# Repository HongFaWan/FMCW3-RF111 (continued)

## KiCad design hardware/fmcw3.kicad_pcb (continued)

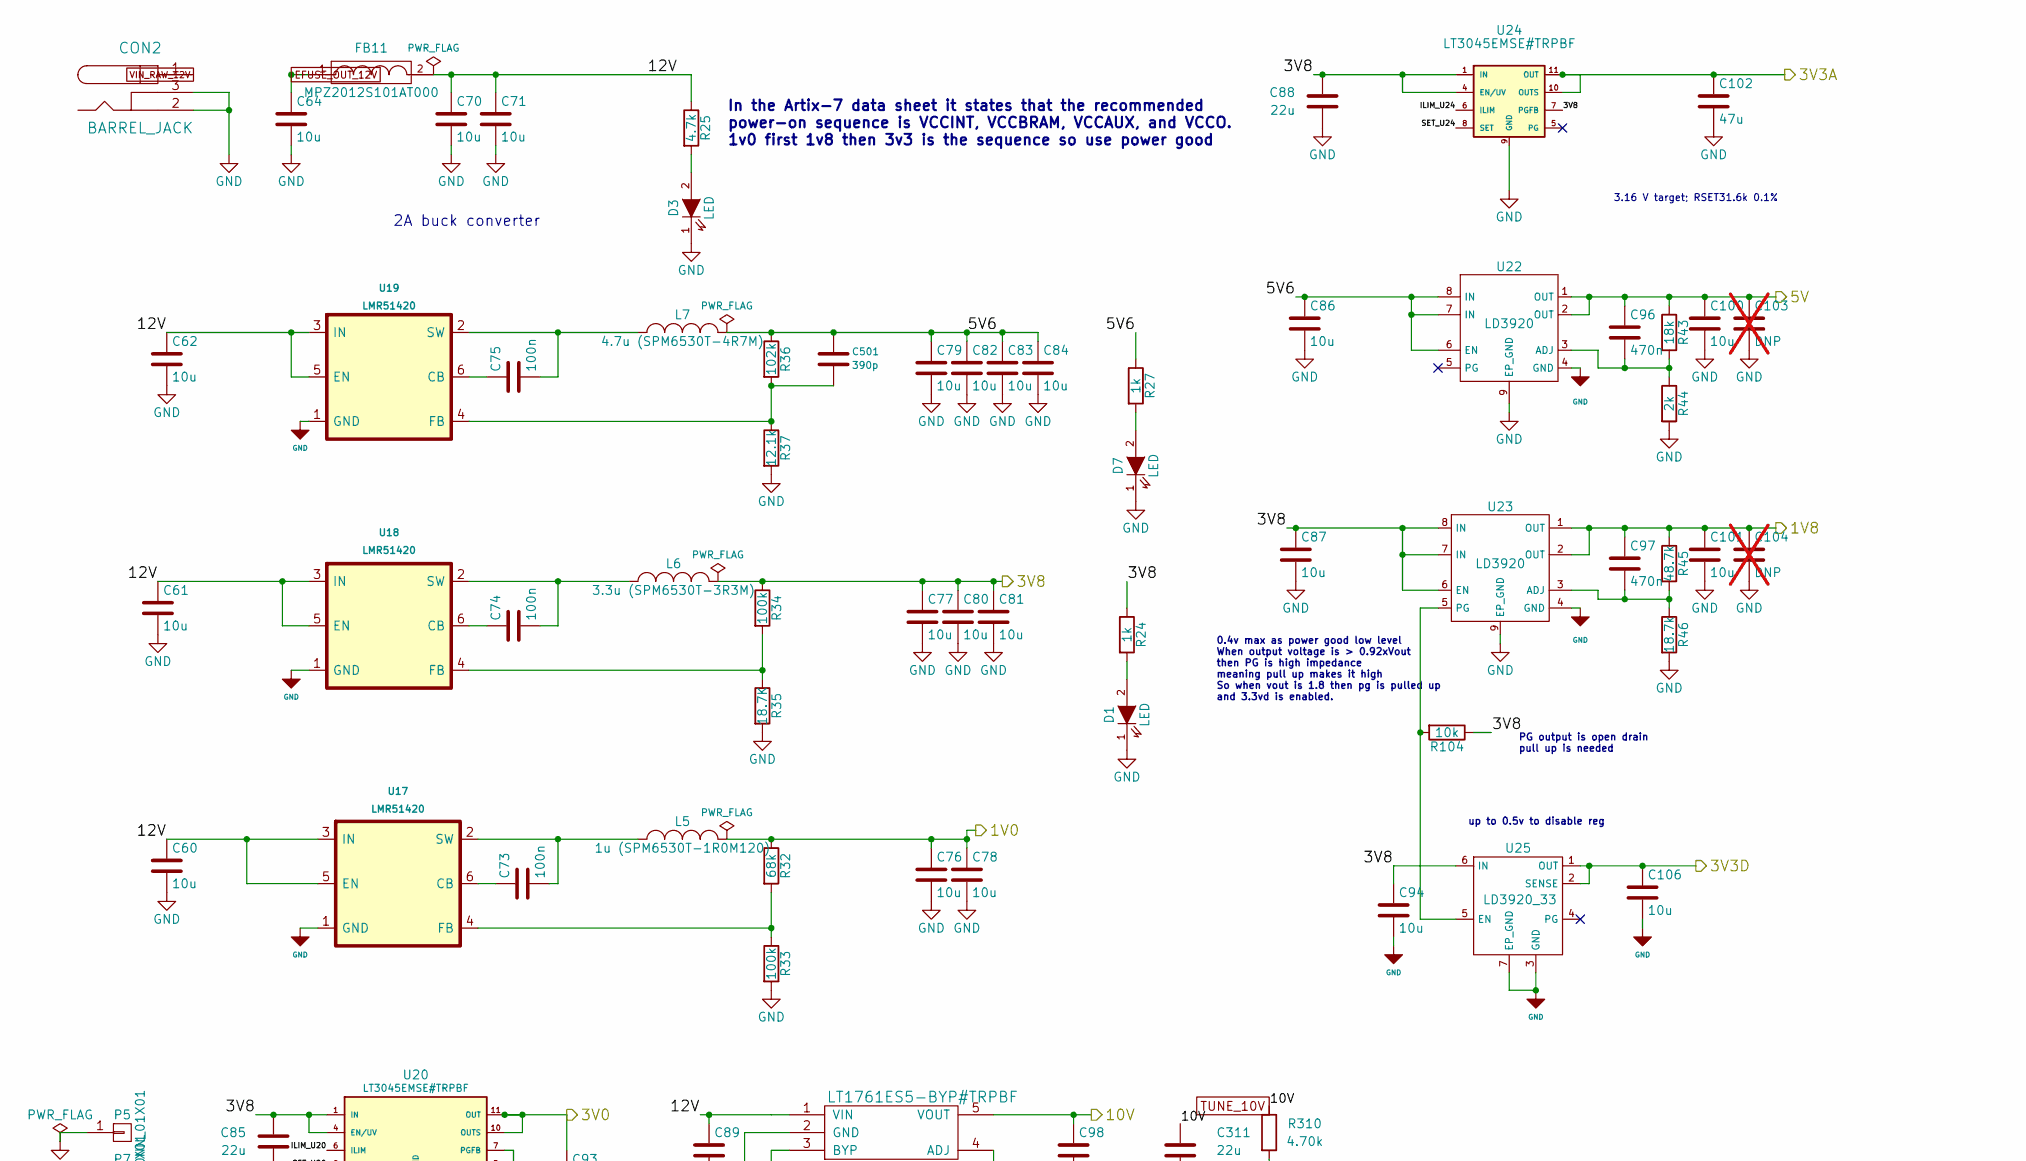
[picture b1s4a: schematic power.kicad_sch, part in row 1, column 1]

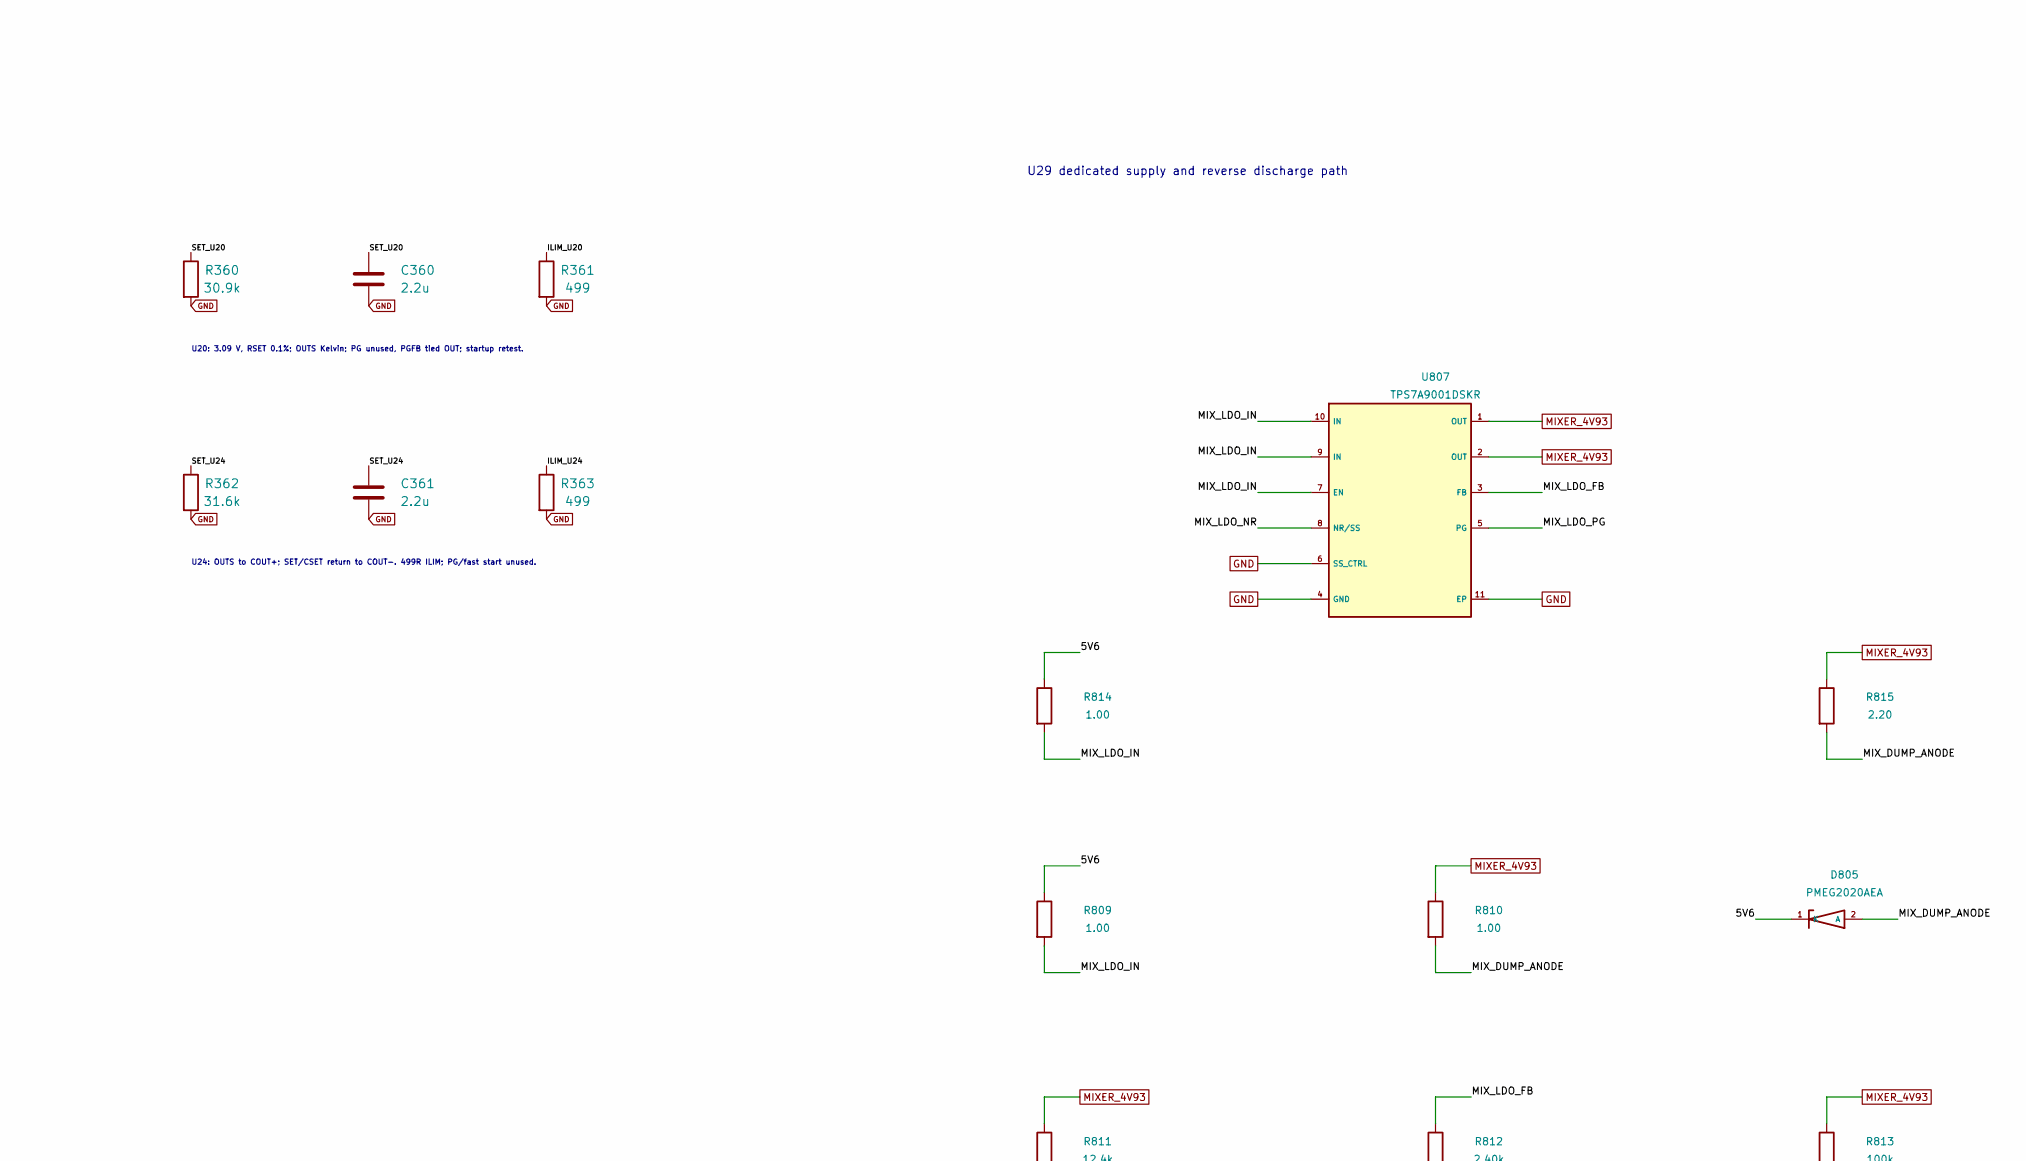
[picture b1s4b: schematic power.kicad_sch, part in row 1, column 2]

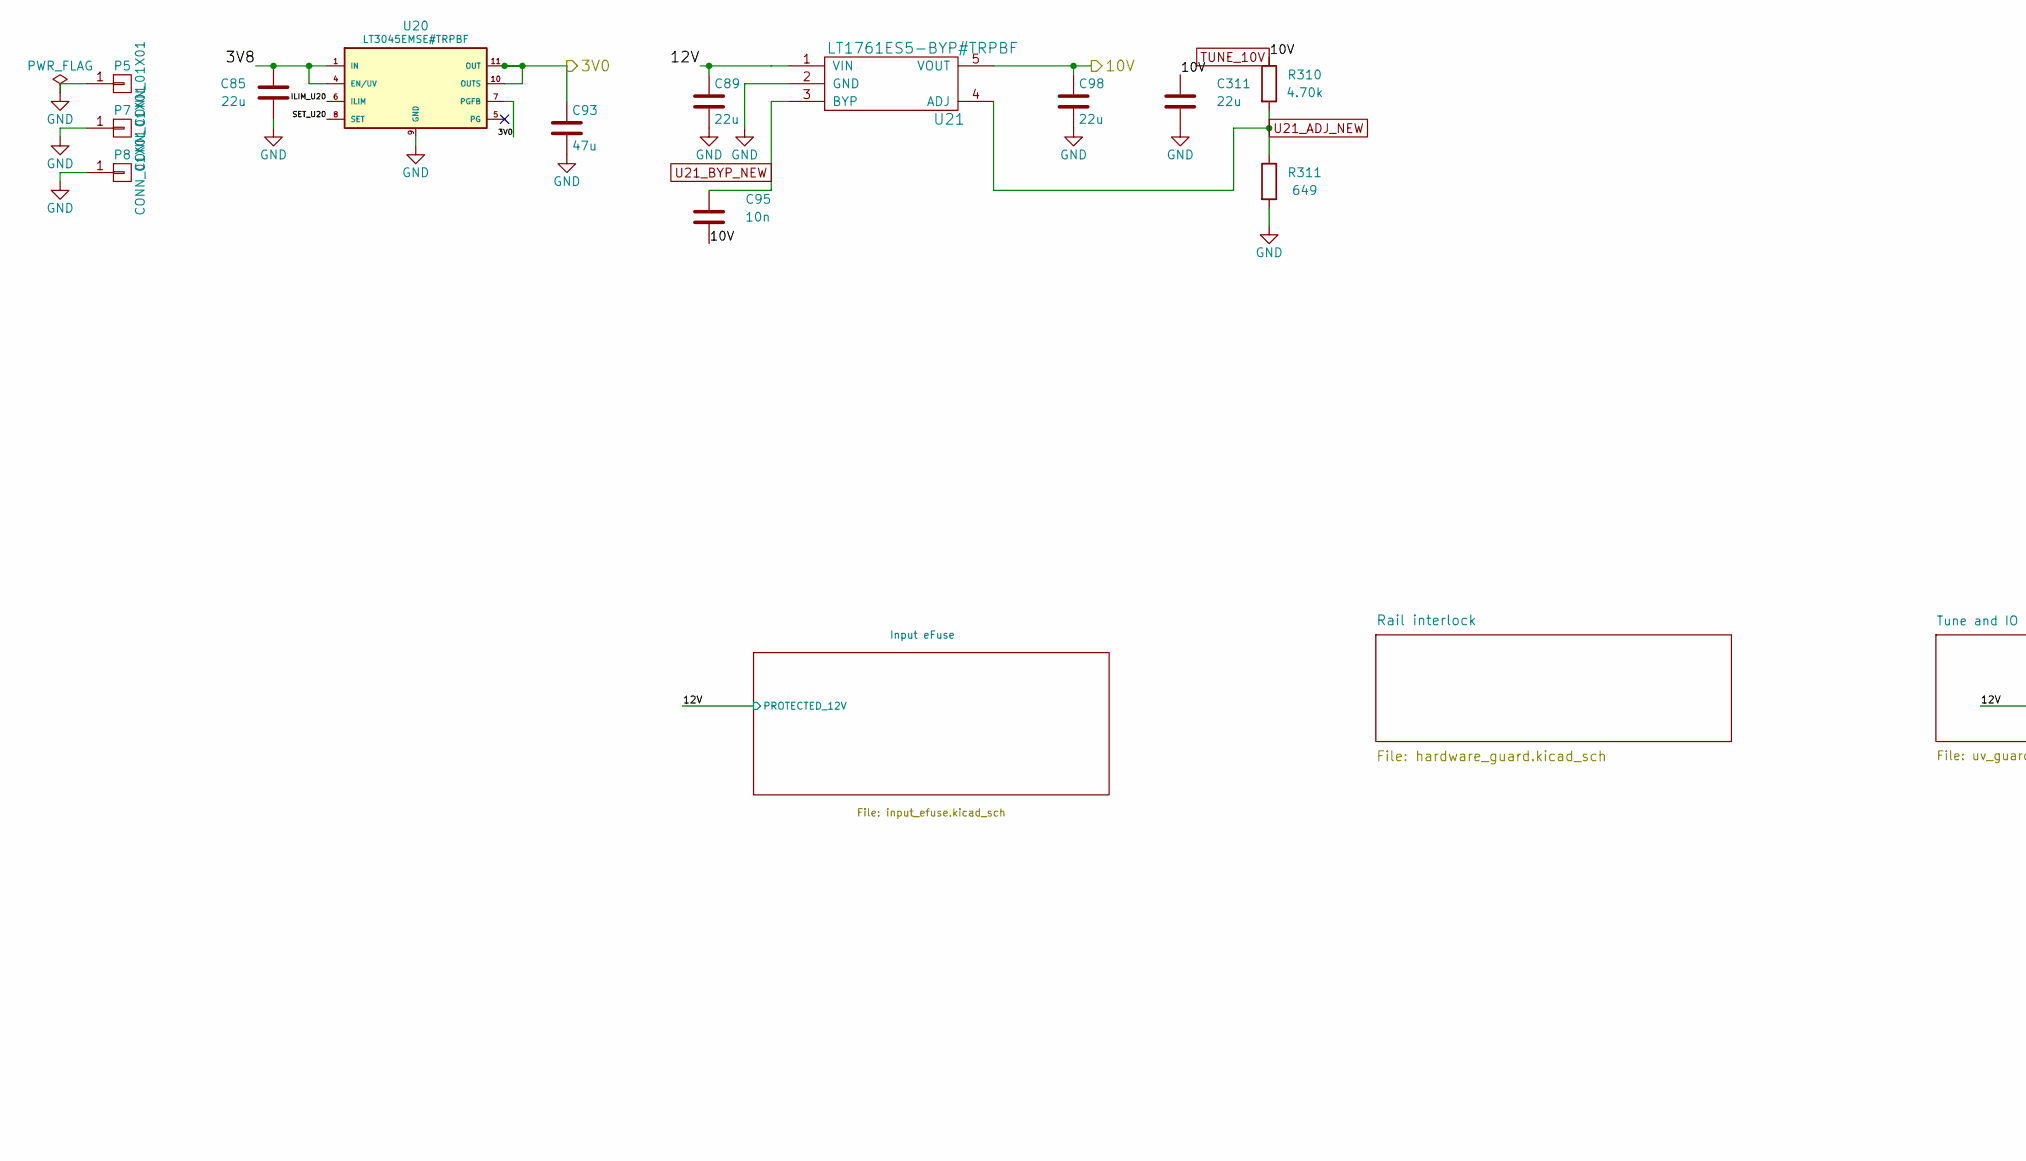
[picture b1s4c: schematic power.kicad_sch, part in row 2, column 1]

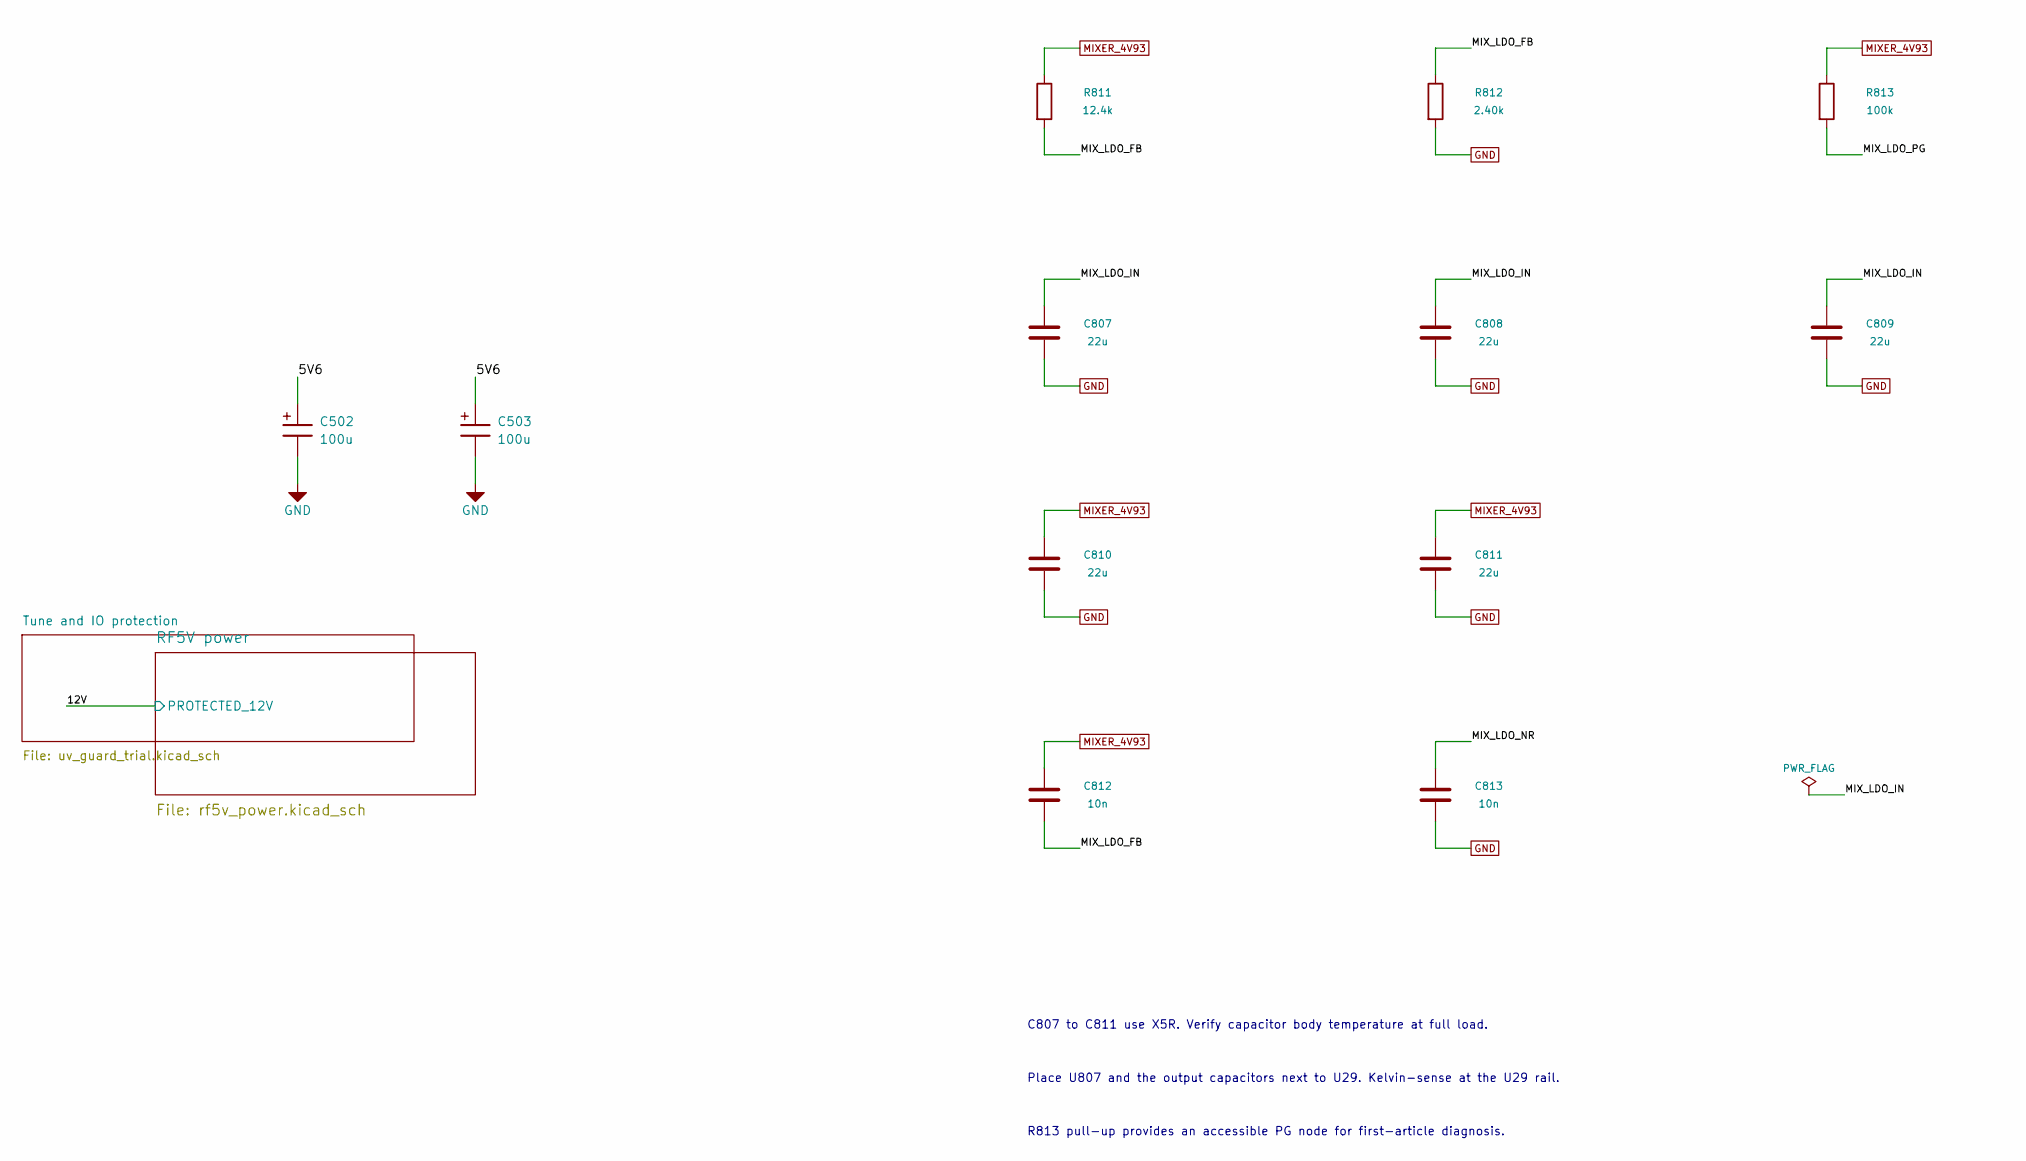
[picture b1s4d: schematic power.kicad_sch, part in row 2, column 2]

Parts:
C60, C61, C62, C64, C70, C71, C76, C77, C78, C79, C80, C81, C82, C83, C84, C86, C87, C94, C100, C101, C106: 10u; SMD_0805
C73, C74, C75: 100n; SMD_0402
C85, C88: 22u; C0805_Murata_GRM21
C89, C311: 22u; C0805_ECO
C93, C102: 47u; C1206_Murata_GRM31
C95: 10n; SMD_0402
C96, C97: 470n; SMD_0402
C98: 22u; SMD_0805
C103, C104: DNP; SMD_0805; not fitted
C360, C361: 2.2u; C0603_Assembly_Courtyard_ECO
C501: 390p; SMD_0402; MPN GRM1555C1H391JA01D
C502, C503: 100u; CP_Panasonic_POSCAP_TQC_D2; MPN 16TQC100MD2
C807, C808, C809, C810, C811: 22u; C_0805_2012Metric; MPN C2012X5R1E226M125AC
C812, C813: 10n; C_0402_1005Metric; MPN GRM1555C1E103GE01D
CON2: BARREL_JACK; PJ002AH_SLOT35
D1, D3, D7: LED; Diode_0603
D805: PMEG2020AEA; D_SOD-323; MPN PMEG2020AEA
FB11: MPZ2012S101AT000; SMD_0805
L5: 1u (SPM6530T-1R0M120); L_TDK_SPM6530T_RF111_PROPOSAL_ONLY; MPN SPM6530T-1R0M120; LCSC C87572
L6: 3.3u (SPM6530T-3R3M); L_TDK_SPM6530T_RF111_PROPOSAL_ONLY; MPN SPM6530T-3R3M; LCSC C76856
L7: 4.7u (SPM6530T-4R7M); L_TDK_SPM6530T_RF111_PROPOSAL_ONLY; MPN SPM6530T-4R7M; LCSC C76857
P5, P7, P8: CONN_01X01; MountingHole_3.2mm_M3_Pad_Via_mod
R24, R27: 1k; SMD_0402
R25: 4.7k; SMD_0402
R32: 68k; SMD_0402
R33, R34: 100k; SMD_0402
R35: 18.7K; SMD_0402
R36: 102k; SMD_0402; Manufacturer Part Number RT0402BRD07102KL
R37: 12.1k; SMD_0402; Manufacturer Part Number ERA-2ARB1212X
R43: 18k; SMD_0402
R44: 2k; SMD_0402
R45: 48.7k; SMD_0402
R46: 18.7k; SMD_0402
R104: 10k; SMD_0402
R310: 4.70k; R0603_ECO; Tolerance and TCR 0.1%, 10 ppm/K; Manufacturer Part Number ERA-3ARB472V
R311: 649; R0603_ECO; Tolerance and TCR 0.1%, 10 ppm/K; Manufacturer Part Number RG1608N-6490-B-T5
R360: 30.9k; R0402_Yageo_Mount_V10; Tolerance 0.1%; MPN RT0402BRD0730K9L; LCSC C852715
R361, R363: 499; R0402_Yageo_Mount_V10
R362: 31.6k; R0402_Panasonic_ERA2A_Mount_RF110; Tolerance 0.1%; MPN ERA-2ARB3162X; LCSC C2090771
R809, R810, R814: 1.00; R_1206_3216Metric; MPN CRCW12061R00FKEAHP
R811: 12.4k; R_0603_1608Metric; MPN ERA3ARW1242V
R812: 2.40k; R_0603_1608Metric; MPN ERA3ARW242V
R813: 100k; R_0402_1005Metric; MPN RT0402BRD07100KL
R815: 2.20; R_1206_3216Metric; MPN CRCW12062R20FKEAHP
U17, U18, U19: LMR51420; SOT23_6
U20, U24: LT3045EMSE#TRPBF; LT3045_MSE12_MFR
U21: LT1761ES5-BYP#TRPBF; LT1761_S5
U22, U23: LD3920; DFN-8-1EP_4x4mm_P0.8mm_EP2.3x3.24mm
U25: LD3920_33; DFN-6-1EP_3x3mm_P0.95mm_EP1.7x2.6mm
U807: TPS7A9001DSKR; Texas_S-PDSO-N10_EP1.2x2mm; MPN TPS7A9001DSKR

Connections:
/1V0: C76.1, C78.1, L5.2, R32.1; also elsewhere on the board
/1V8: C97.1, C101.1, C104.1, R45.1, U23.1 (OUT), U23.2 (OUT); also elsewhere on the board
/3V0: C93.1, U20.7 (PGFB), U20.10 (OUTS), U20.11 (OUT), U20.12 (OUT); also elsewhere on the board
/3V3A: C102.1, U24.10 (OUTS), U24.11 (OUT), U24.12 (OUT); also elsewhere on the board
/3V8: C77.1, C80.1, C81.1, C85.1, C87.1, C88.1, C94.1, L6.2, R24.1, R34.1, R104.1, U20.1 (IN), U20.2 (IN), U20.3 (IN), U20.4 (EN/UV), U23.6 (EN), U23.7 (VIN), U23.8 (VIN), U24.1 (IN), U24.2 (IN), U24.3 (IN), U24.4 (EN/UV), U24.7 (PGFB), U25.6 (VIN); also elsewhere on the board
/5V: C96.1, C100.1, C103.1, R43.1, U22.1 (OUT), U22.2 (OUT); also elsewhere on the board
/power/5V6: C79.1, C82.1, C83.1, C84.1, C86.1, C501.1, C502.1, C503.1, D805.1 (K), L7.2, R27.1, R36.1, R809.1, R814.1, U22.6 (EN), U22.7 (VIN), U22.8 (VIN)
/power/12V: C60.1, C61.1, C62.1, C70.1, C71.1, C89.1, FB11.2, R25.1, U17.3 (IN), U17.5 (EN), U18.3 (IN), U18.5 (EN), U19.3 (IN), U19.5 (EN), U21.1 (IN); also elsewhere on the board
/power/ILIM_U20: R361.1, U20.6 (ILIM)
/power/ILIM_U24: R363.1, U24.6 (ILIM)
/power/MIX_DUMP_ANODE: D805.2 (A), R810.2, R815.2
/power/MIX_LDO_FB: C812.2, R811.2, R812.1, U807.3 (FB)
/power/MIX_LDO_IN: C807.1, C808.1, C809.1, R809.2, R814.2, U807.7 (EN), U807.9 (IN), U807.10 (IN)
/power/MIX_LDO_NR: C813.1, U807.8 (NR/SS)
/power/MIX_LDO_PG: R813.2, U807.5 (PG)
/power/SET_U20: C360.1, R360.1, U20.8 (SET)
/power/SET_U24: C361.1, R362.1, U24.8 (SET)
EFUSE_OUT_12V: C64.1, FB11.1; also elsewhere on the board
GND: C60.2, C61.2, C62.2, C64.2, C70.2, C71.2, C76.2, C77.2, C78.2, C79.2, C80.2, C81.2, C82.2, C83.2, C84.2, C85.2, C86.2, C87.2, C88.2, C89.2, C93.2, C94.2, C98.2, C100.2, C101.2, C102.2, C103.2, C104.2, C106.2, C311.2, C360.2, C361.2, C502.2, C503.2, C807.2, C808.2, C809.2, C810.2, C811.2, C813.2, CON2.2, CON2.3, D1.1 (K), D3.1 (K), D7.1 (K), P5.1, P7.1, P8.1, R33.2, R35.2, R37.2, R44.2, R46.2, R311.2, R360.2, R361.2, R362.2, R363.2, R812.2, U17.1 (GND), U18.1 (GND), U19.1 (GND), U20.9 (GND), U20.13 (GND), U21.2 (GND), U22.4 (GND), U22.9 (PAD), U23.4 (GND), U23.9 (PAD), U24.9 (GND), U24.13 (GND), U25.3 (GND), U25.7 (PAD), U807.4 (GND), U807.6 (SS_CTRL), U807.11 (EP); also elsewhere on the board
MIXER_4V93: C810.1, C811.1, C812.1, R810.1, R811.1, R813.1, R815.1, U807.1 (OUT), U807.2 (OUT); also elsewhere on the board
unnamed: D1.2 (A), R24.2
unnamed: D3.2 (A), R25.2
unnamed: D7.2 (A), R27.2
unnamed: C73.1, U17.6 (CB)
unnamed: R32.2, R33.1, U17.4 (FB)
unnamed: C73.2, L5.1, U17.2 (SW)
unnamed: C74.1, U18.6 (CB)
unnamed: R34.2, R35.1, U18.4 (FB)
unnamed: C74.2, L6.1, U18.2 (SW)
unnamed: C75.1, U19.6 (CB)
unnamed: C501.2, R36.2, R37.1, U19.4 (FB)
unnamed: C75.2, L7.1, U19.2 (SW)
unnamed: C96.2, R43.2, R44.1, U22.3 (ADJ)
unnamed: C97.2, R45.2, R46.1, U23.3 (ADJ)
unnamed: R104.2, U23.5 (PG), U25.5 (EN)
TUNE_10V: C95.2, C98.1, C311.1, R310.1, U21.5 (OUT); also elsewhere on the board
U21_ADJ_NEW: R310.2, R311.1, U21.4 (ADJ)
U21_BYP_NEW: C95.1, U21.3 (BYP)
VIN_RAW_12V: CON2.1; also elsewhere on the board

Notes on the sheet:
up to 0.5v to disable reg
0.4v max as power good low level When output voltage is > 0.92xVout then PG is high impedance meaning pull up makes it high So when vout is 1.8 then pg is pulled up and 3.3vd is enabled.
PG output is open drain pull up is needed
In the Artix-7 data sheet it states that the recommended power-on sequence is VCCINT, VCCBRAM, VCCAUX, and VCCO. 1v0 first 1v8 then 3v3 is the sequence so use power good
2A buck converter
3.16 V target; RSET31.6k 0.1%
U20: 3.09 V, RSET 0.1%; OUTS Kelvin; PG unused, PGFB tied OUT; startup retest.
U24: OUTS to COUT+; SET/CSET return to COUT-. 499R ILIM; PG/fast start unused.
U29 dedicated supply and reverse discharge path
C807 to C811 use X5R. Verify capacitor body temperature at full load.
Place U807 and the output capacitors next to U29. Kelvin-sense at the U29 rail.
R813 pull-up provides an accessible PG node for first-article diagnosis.

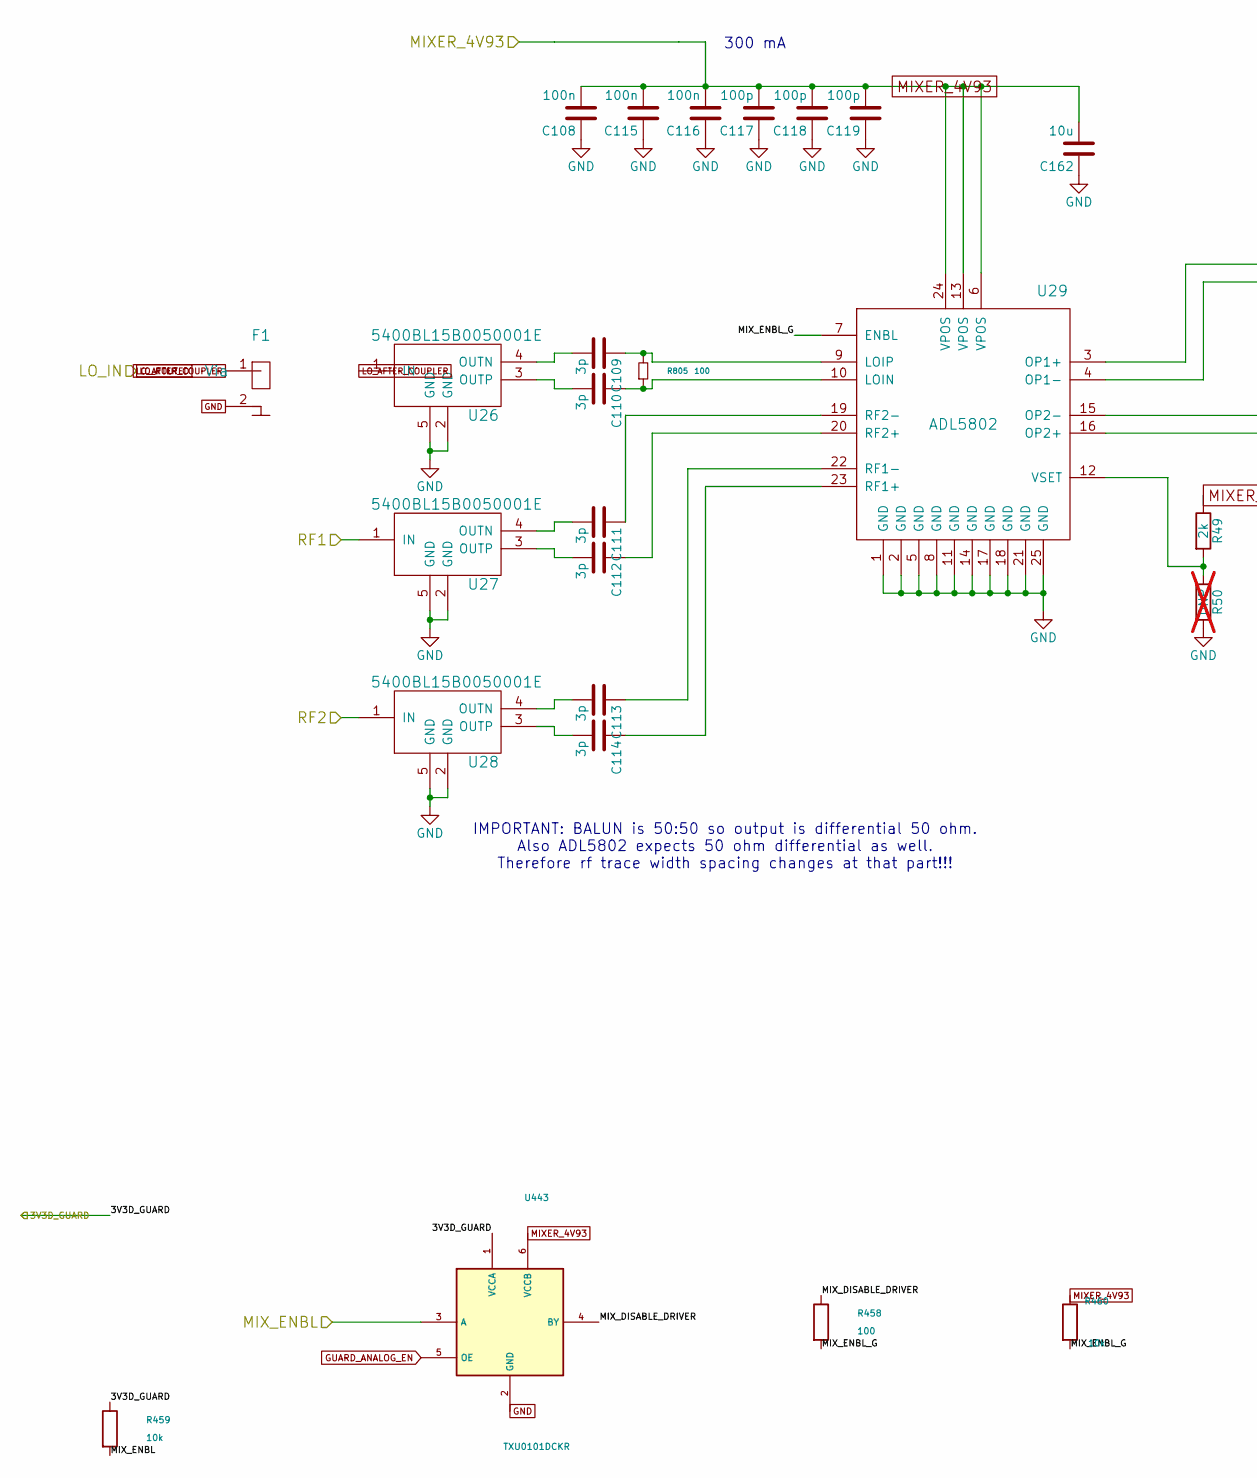
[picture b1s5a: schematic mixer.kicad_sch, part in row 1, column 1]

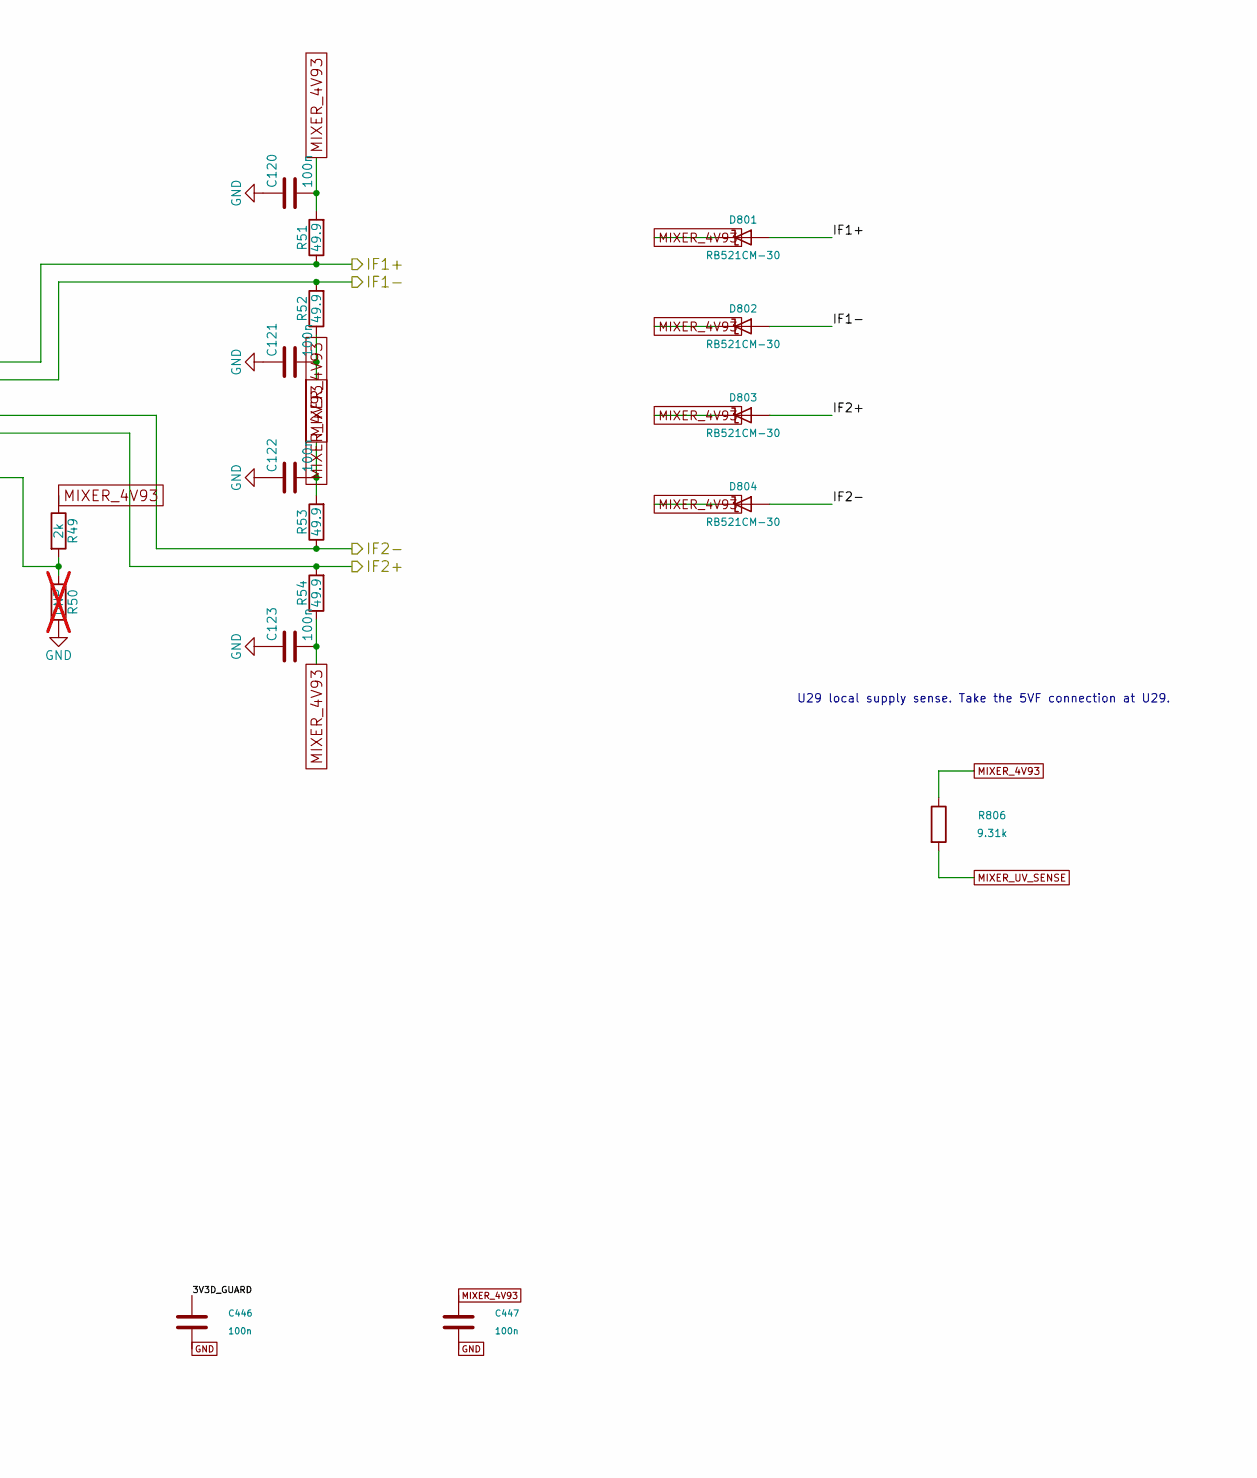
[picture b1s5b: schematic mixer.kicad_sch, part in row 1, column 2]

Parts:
C108, C115, C116, C120, C121, C122, C123: 100n; SMD_0402
C109, C110, C111, C112, C113, C114: 3p; SMD_0402; Tolerance +/-0.1pF; Voltage 50V; MPN GJM1555C1H3R0BB01D; LCSC C88891
C117, C118, C119: 100p; SMD_0402
C162: 10u; SMD_0805
C446, C447: 100n; C_0402_Murata_GRM155_Mount22; MPN GRM155R71H104KE14D; LCSC C77020
D801, D802, D803, D804: RB521CM-30; ROHM_VMN2M; Manufacturer Part Number RB521CM-30T2R
F1: Via; RF_via
R49: 2k; SMD_0402
R50: DNP; SMD_0402; not fitted
R51, R52, R53, R54: 49.9; SMD_0402; MPN SG73P1EWTTP49R9F
R458: 100; R_0402_Yageo_Mount22; MPN RC0402FR-07100RL; LCSC C106232
R459, R460: 10k; R_0402_Yageo_Mount22; MPN RT0402BRD0710KL; LCSC C190095
R805: 100; R_0201_0603Metric_LO; MPN ERJ1GNF1000C
R806: 9.31k; R_0603_1608Metric; MPN ERA3ARW9311V
U26, U27, U28: 5400BL15B0050001E; 5400BL15B050E
U29: ADL5802; QFN-24-1EP_4x4mm_Pitch0.5mm
U443: TXU0101DCKR; TI_DCK6_0p9x0p4_MFR; MPN TXU0101DCKR; LCSC C5217868

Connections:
/MIX_ENBL: R459.2, U443.3 (A); also elsewhere on the board
/RF1: U27.1 (IN); also elsewhere on the board
/RF2: U28.1 (IN); also elsewhere on the board
/mixer/IF1+: D801.2 (A), R51.1, U29.3 (OP1+); also elsewhere on the board
/mixer/IF1-: D802.2 (A), R52.2, U29.4 (OP1-); also elsewhere on the board
/mixer/IF2+: D803.2 (A), R54.2, U29.16 (OP2+); also elsewhere on the board
/mixer/IF2-: D804.2 (A), R53.1, U29.15 (OP2-); also elsewhere on the board
/mixer/MIX_DISABLE_DRIVER: R458.1, U443.4 (BY)
/mixer/MIX_ENBL_G: R458.2, R460.2, U29.7 (ENBL)
GND: C108.1, C115.1, C116.1, C117.1, C118.1, C119.1, C120.1, C121.1, C122.1, C123.1, C162.1, C446.2, C447.2, F1.2, R50.2, U26.2 (GND), U26.5 (GND), U27.2 (GND), U27.5 (GND), U28.2 (GND), U28.5 (GND), U29.1 (GND), U29.2 (GND), U29.5 (GND), U29.8 (GND), U29.11 (GND), U29.14 (GND), U29.17 (GND), U29.18 (GND), U29.21 (GND), U29.25 (GND), U443.2 (GND); also elsewhere on the board
GUARD_ANALOG_EN: U443.5 (OE); also elsewhere on the board
LO_AFTER_COUPLER: F1.1, U26.1 (IN); also elsewhere on the board
MIXER_4V93: C108.2, C115.2, C116.2, C117.2, C118.2, C119.2, C120.2, C121.2, C122.2, C123.2, C162.2, C447.1, D801.1 (K), D802.1 (K), D803.1 (K), D804.1 (K), R49.1, R51.2, R52.1, R53.2, R54.1, R460.1, R806.1, U29.6 (VPOS), U29.13 (VPOS), U29.24 (VPOS), U443.6 (VCCB); also elsewhere on the board
MIXER_UV_SENSE: R806.2; also elsewhere on the board
unnamed: C109.2, U26.4 (OUTN)
unnamed: C110.2, U26.3 (OUTP)
unnamed: C111.2, U27.4 (OUTN)
unnamed: C112.2, U27.3 (OUTP)
unnamed: C113.2, U28.4 (OUTN)
unnamed: C114.2, U28.3 (OUTP)
unnamed: C110.1, R805.2, U29.10 (LOIN)
unnamed: C109.1, R805.1, U29.9 (LOIP)
unnamed: C114.1, U29.23 (RF1+)
unnamed: C113.1, U29.22 (RF1-)
unnamed: C112.1, U29.20 (RF2+)
unnamed: C111.1, U29.19 (RF2-)
unnamed: R49.2, R50.1, U29.12 (VSET)

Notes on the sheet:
300 mA
IMPORTANT: BALUN is 50:50 so output is differential 50 ohm. Also ADL5802 expects 50 ohm differential as well. Therefore rf trace width spacing changes at that part!!!
U29 local supply sense. Take the 5VF connection at U29.

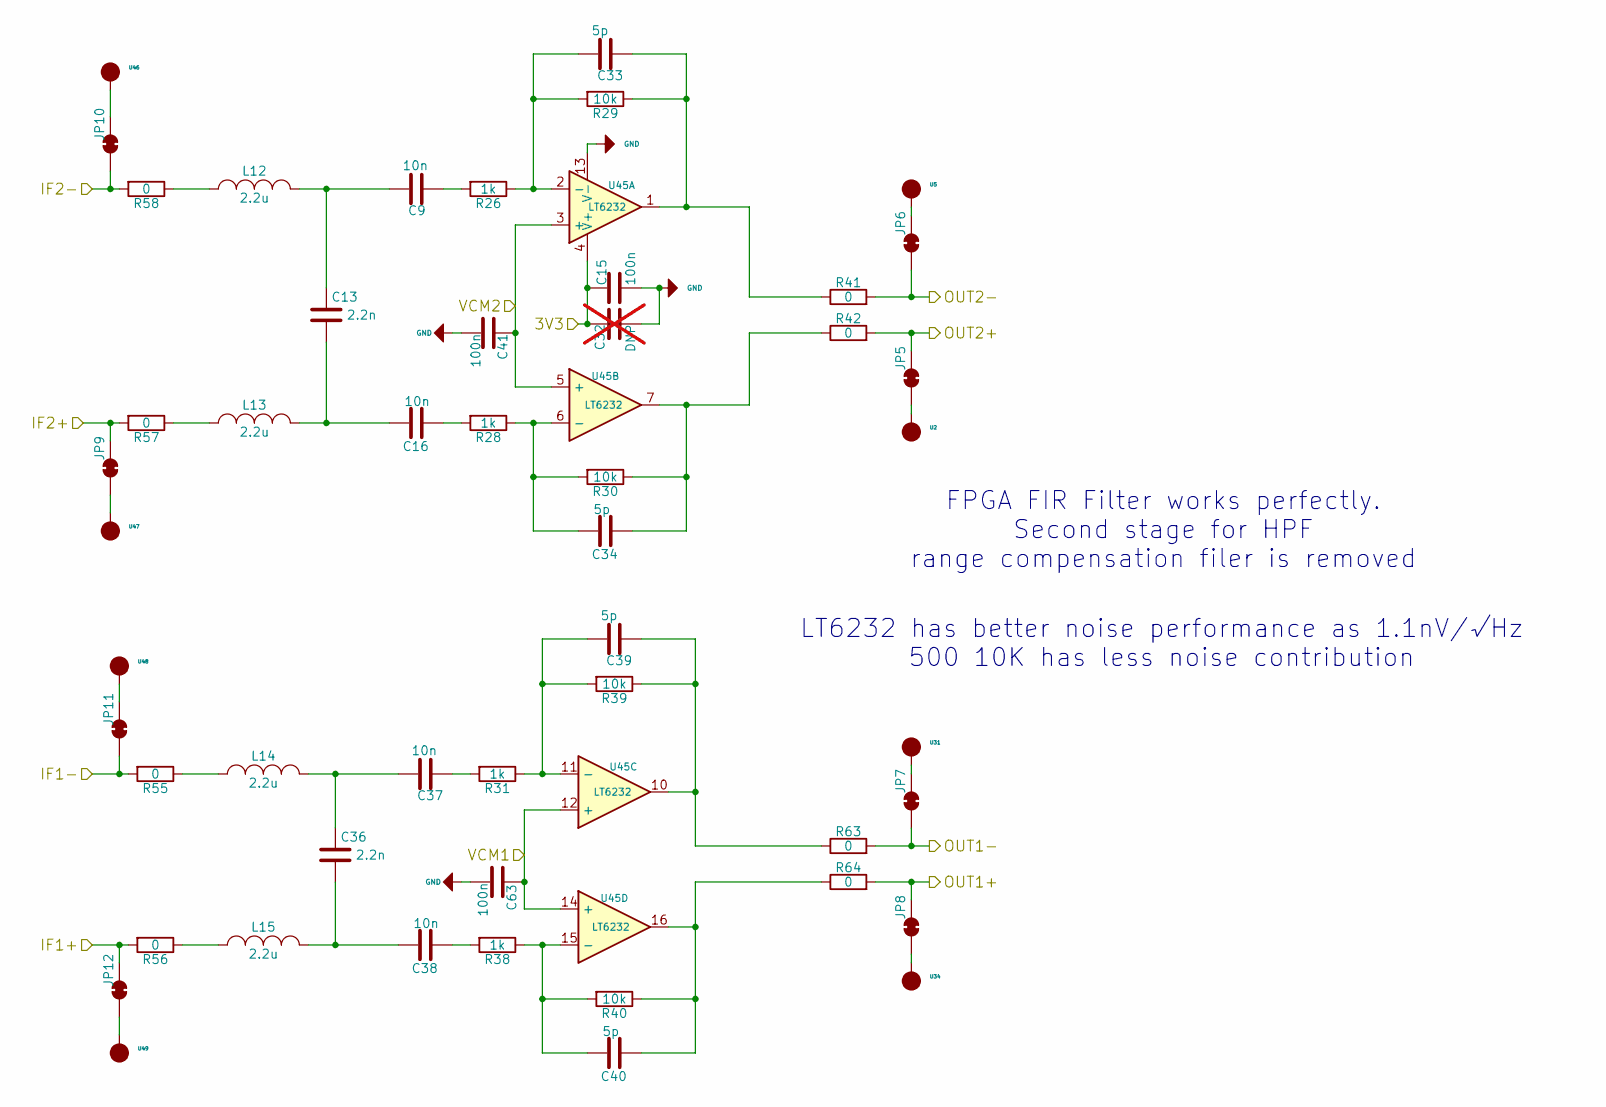
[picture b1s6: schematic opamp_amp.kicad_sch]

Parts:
C9, C16, C37, C38: 10n; SMD_0402
C13, C36: 2.2n; SMD_0402
C15, C41, C63: 100n; SMD_0402
C32: DNP; SMD_0805; not fitted
C33, C34, C39, C40: 5p; SMD_0402
JP5, JP6, JP7, JP8, JP9, JP10, JP11, JP12: SolderJumper_2_Bridged; SolderPad_2_Bridge
L12, L13, L14, L15: 2.2u; SMD_0805
R26, R28, R31, R38: 1k; SMD_0402
R29, R30, R39, R40: 10k; SMD_0402
R41, R42, R55, R56, R57, R58, R63, R64: 0; SMD_0402
U2, U5, U31, U34, U46, U47, U48, U49: SolderPad_1_Circle; SolderPad_1_1.0mm_SMD_Circle
U45: LT6232; SSOP16_3.9x4.9mm_P0.635mm

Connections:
/3V3A: C15.1, C32.1, U45.4 (V+); also elsewhere on the board
/ADC1+: JP8.2 (B), R64.2; also elsewhere on the board
/ADC1-: JP7.1 (A), R63.2; also elsewhere on the board
/ADC2+: JP5.2 (B), R42.2; also elsewhere on the board
/ADC2-: JP6.1 (A), R41.2; also elsewhere on the board
/ADC_VCMA: C41.1, U45.3 (+), U45.5 (+); also elsewhere on the board
/ADC_VCMB: C63.1, U45.12 (+), U45.14 (+); also elsewhere on the board
/mixer/IF1+: JP12.2 (B), R56.2; also elsewhere on the board
/mixer/IF1-: JP11.1 (A), R55.2; also elsewhere on the board
/mixer/IF2+: JP9.2 (B), R57.2; also elsewhere on the board
/mixer/IF2-: JP10.1 (A), R58.2; also elsewhere on the board
GND: C15.2, C32.2, C41.2, C63.2, U45.13 (V-); also elsewhere on the board
unnamed: C9.1, R26.2
unnamed: C9.2, C13.1, L12.2
unnamed: C13.2, C16.2, L13.2
unnamed: C16.1, R28.2
unnamed: C33.1, R29.1, R41.1, U45.1
unnamed: C34.1, R30.1, R42.1, U45.7
unnamed: C36.1, C37.2, L14.2
unnamed: C36.2, C38.2, L15.2
unnamed: C37.1, R31.2
unnamed: C38.1, R38.2
unnamed: C39.1, R39.1, R63.1, U45.10
unnamed: C40.1, R40.1, R64.1, U45.16
unnamed: JP5.1 (A), U2.1
unnamed: JP6.2 (B), U5.1
unnamed: JP7.2 (B), U31.1
unnamed: JP8.1 (A), U34.1
unnamed: JP9.1 (A), U47.1
unnamed: JP10.2 (B), U46.1
unnamed: JP11.2 (B), U48.1
unnamed: JP12.1 (A), U49.1
unnamed: L12.1, R58.1
unnamed: L13.1, R57.1
unnamed: L14.1, R55.1
unnamed: L15.1, R56.1
unnamed: C33.2, R26.1, R29.2, U45.2 (-)
unnamed: C34.2, R28.1, R30.2, U45.6 (-)
unnamed: C39.2, R31.1, R39.2, U45.11 (-)
unnamed: C40.2, R38.1, R40.2, U45.15 (-)

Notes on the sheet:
LT6232 has better noise performance as 1.1nV/√Hz 500 10K has less noise contribution
FPGA FIR Filter works perfectly. Second stage for HPF range compensation filer is removed
